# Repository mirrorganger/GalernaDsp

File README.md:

# Galerna DSP

Galerna DSP is a KiCad hardware project for an STM32-based audio effects board: two
audio channels in/out, 8 potentiometers, footswitches/buttons, an OLED display, and a
microSD slot, all built around an STM32F405.

Full design write-up — requirements, as-built BOM, power budget, codec/amp circuit
notes — lives in **[docs/Design.md](docs/Design.md)**.

## Repository layout

| Path | Contents |
|---|---|
| `GalernaDsp.kicad_pro` / `.kicad_pcb` / `.kicad_sch` | Top-level KiCad project and root schematic sheet |
| `power.kicad_sch`, `mcu.kicad_sch`, `audio_codec.kicad_sch`, `input_control.kicad_sch` | The four schematic sub-sheets |
| `libraries/Galerna/` | Project-specific KiCad symbol/footprint/3D-model library |
| `cubeMx/` | STM32CubeMX-generated firmware project for the STM32F405RGT6 (peripheral init only, no application code yet) |
| `jlcpcb/` | Manufacturing outputs for JLCPCB: gerbers, drill files, BOM/CPL for assembly |
| `docs/` | Design documentation |
| `GalernaDsp.xlsx` / `.csv` | Bill of materials |

## Opening the project

Open `GalernaDsp.kicad_pro` in KiCad (7.x). The root schematic pulls in the four
sub-sheets listed above; the PCB is a single `GalernaDsp.kicad_pcb`.

## Firmware

`cubeMx/` is a standard STM32CubeMX + CMake project. Regenerate from `cubeMx/Galerna.ioc`
in STM32CubeMX if peripheral config changes; build with CMake/CMakePresets as usual for
an STM32F4 target.

## Manufacturing

Gerbers, drill files, and JLCPCB assembly data (BOM/CPL) are pre-generated under
`jlcpcb/production_files/`.

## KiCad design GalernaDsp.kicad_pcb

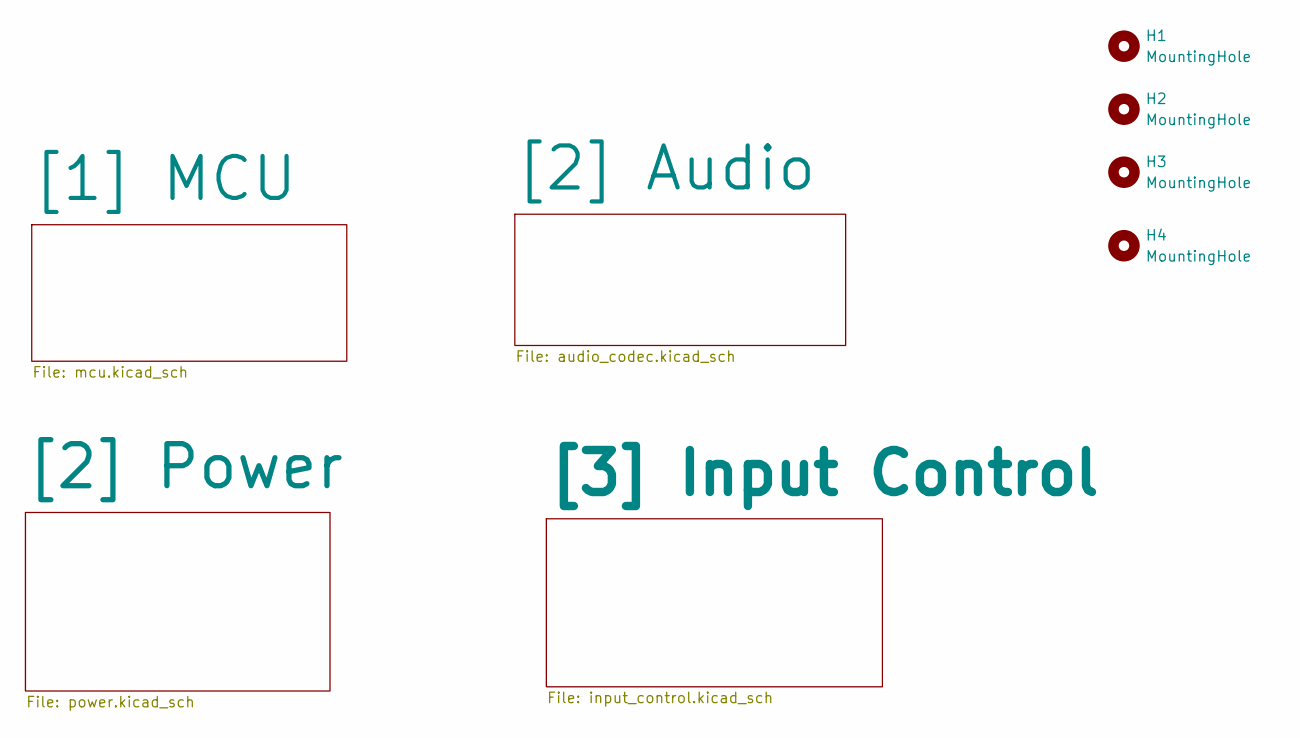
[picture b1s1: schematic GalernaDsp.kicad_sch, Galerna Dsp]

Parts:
H1, H2, H3, H4: MountingHole; MountingHole_3.2mm_M3_DIN965_Pad_TopBottom

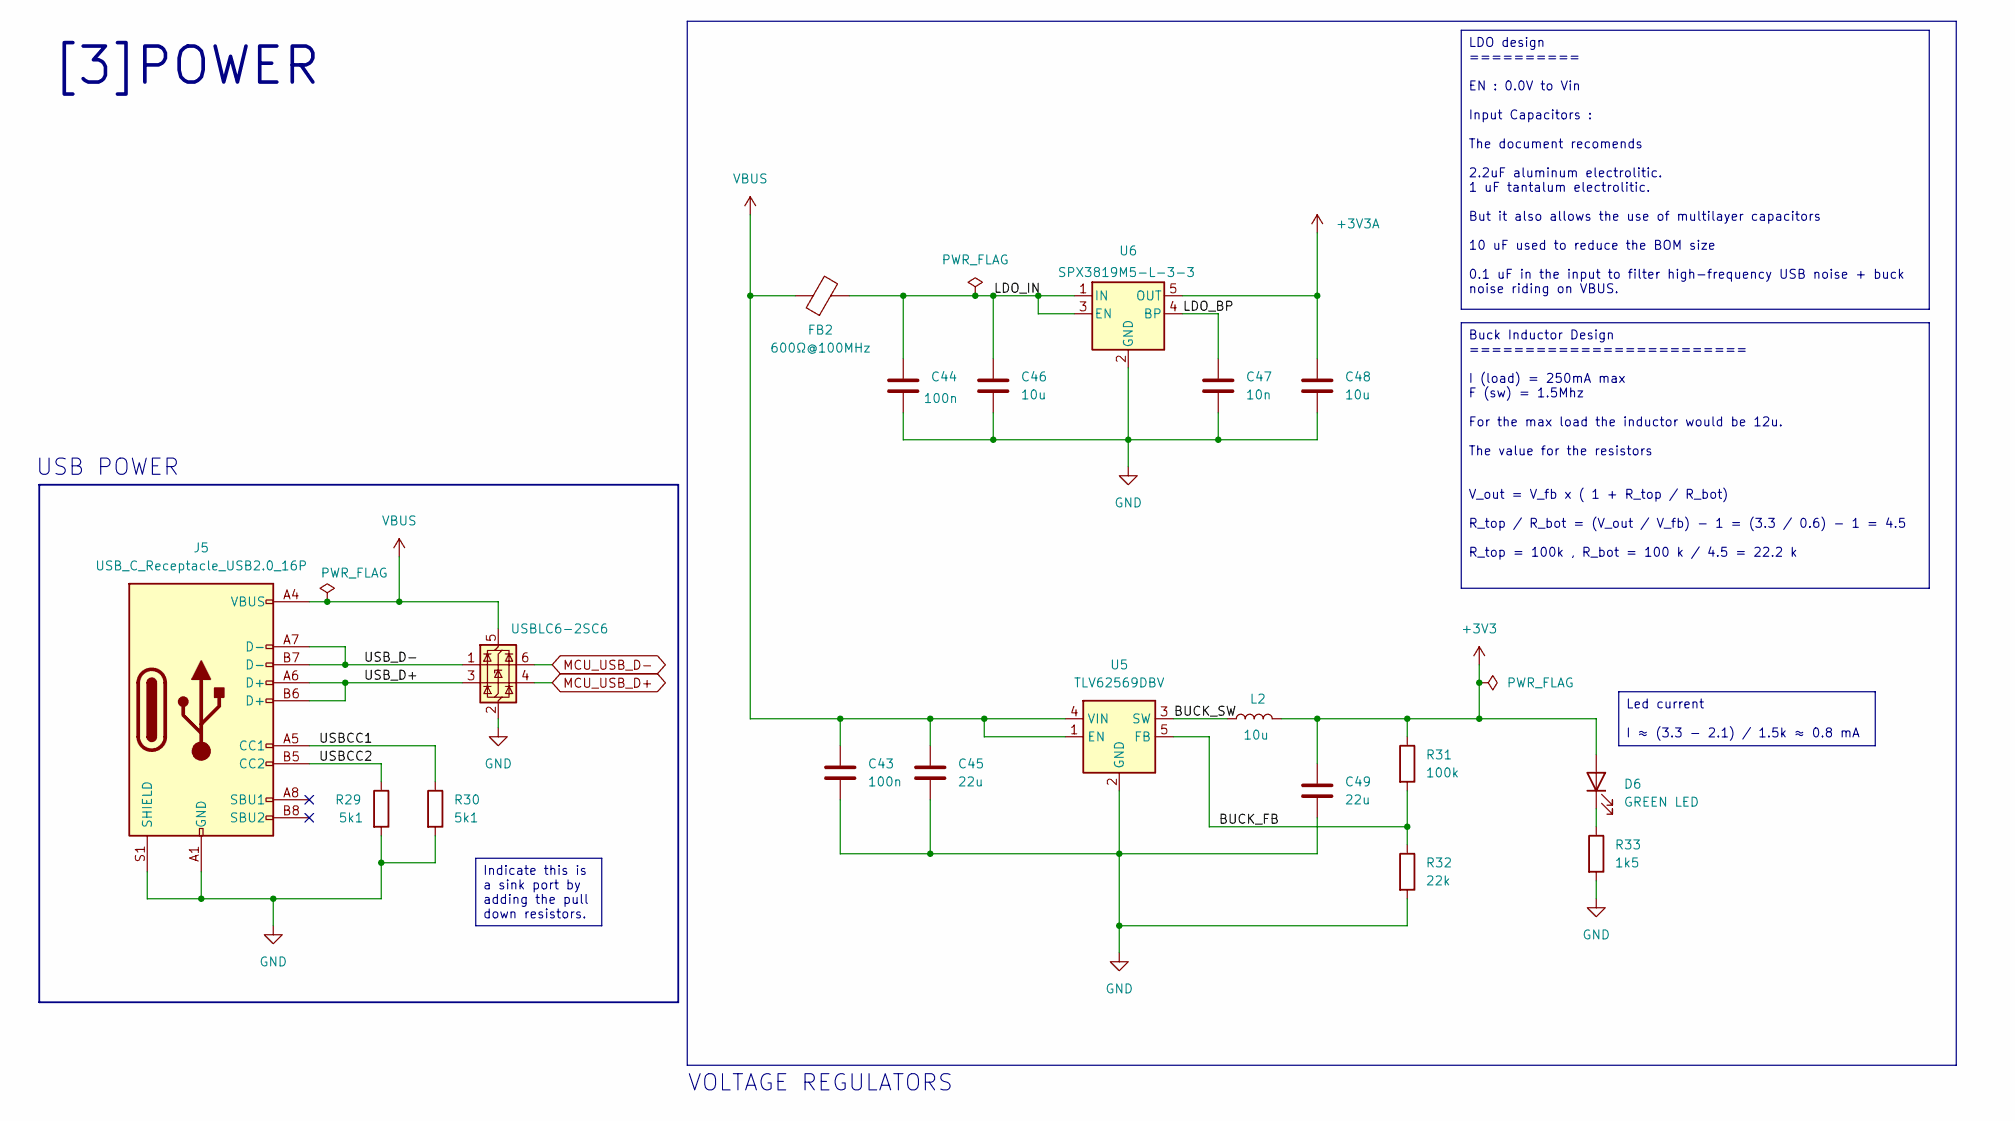
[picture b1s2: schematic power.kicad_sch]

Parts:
C43, C44: 100n; C_0402_1005Metric
C45, C49: 22u; C_0805_2012Metric
C46, C48: 10u; C_0603_1608Metric
C47: 10n; C_0402_1005Metric
D6: GREEN LED; LED_0805_2012Metric
FB2: 600Ω@100MHz; R_0805_2012Metric; Manufacturer Part GZ2012D601TF; LCSC Part C1017
J5: USB_C_Receptacle_USB2.0_16P; USB_C_Receptacle_GCT_USB4105-xx-A_16P_TopMnt_Horizontal; Manufacturer Part TYPE-C 16PIN 2MD(073); LCSC Part C2765186
L2: 10u; L_Sunlord_MWSA0618S; Manufacturer Part MWSA0618S-100MT; LCSC Part C132135
R29, R30: 5k1; R_0402_1005Metric
R31: 100k; R_0402_1005Metric
R32: 22k; R_0402_1005Metric
R33: 1k5; R_0402_1005Metric
U4: USBLC6-2SC6; SOT-23-6; Manufacturer Part USBLC6-2SC6; LCSC Part C7519
U5: TLV62569DBV; SOT-23-5; Manufacturer Part TLV62569DBVR; LCSC Part C141836
U6: SPX3819M5-L-3-3; SOT-23-5; Manufacturer Part SPX3819M5-L-3-3; LCSC Part C20617301

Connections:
+3V3: C49.1, D6.2 (A), L2.2, R31.1; also elsewhere on the board
+3V3A: C48.1, U6.5 (OUT); also elsewhere on the board
/[2] Power/BUCK_FB: R31.2, R32.1, U5.5 (FB)
/[2] Power/BUCK_SW: L2.1, U5.3 (SW)
/[2] Power/LDO_BP: C47.1, U6.4 (BP)
/[2] Power/LDO_IN: C44.1, C46.1, FB2.2, U6.1 (IN), U6.3 (EN)
/[2] Power/USBCC1: J5.A5 (CC1), R30.1
/[2] Power/USBCC2: J5.B5 (CC2), R29.1
/[2] Power/USB_D+: J5.A6 (D+), J5.B6 (D+), U4.3 (I/O2)
/[2] Power/USB_D-: J5.A7 (D-), J5.B7 (D-), U4.1 (I/O1)
GND: C43.2, C44.2, C45.2, C46.2, C47.2, C48.2, C49.2, J5.A1 (GND), J5.A12 (GND), J5.B1 (GND), J5.B12 (GND), J5.S1 (SHIELD), R29.2, R30.2, R32.2, R33.2, U4.2 (GND), U5.2 (GND), U6.2 (GND); also elsewhere on the board
MCU_USB_D+: U4.4 (I/O2); also elsewhere on the board
MCU_USB_D-: U4.6 (I/O1); also elsewhere on the board
unnamed: D6.1 (K), R33.1
VBUS: C43.1, C45.1, FB2.1, J5.A4 (VBUS), J5.A9 (VBUS), J5.B4 (VBUS), J5.B9 (VBUS), U4.5 (VBUS), U5.1 (EN), U5.4 (VIN)

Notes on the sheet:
VOLTAGE REGULATORS
USB POWER
[3]POWER
Indicate this is a sink port by adding the pull down resistors.
Led current I ≈ (3.3 - 2.1) / 1.5k ≈ 0.8 mA
LDO design ========== EN : 0.0V to Vin Input Capacitors : The document recomends 2.2uF aluminum electrolitic. 1 uF tantalum electrolitic. But it also allows the use of multilayer capacitors 10 uF used to reduce the BOM size 0.1 uF in the input to filter high-frequency USB noise + buck noise riding 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
Buck Inductor Design ========================= I (load) = 250mA max F (sw) = 1.5Mhz For the max load the inductor would be 12u. The value for the resistors V_out = V_fb x ( 1 + R_top / R_bot) R_top / R_bot = (V_out / V_fb) - 1 = (3.3 / 0.6) - 1 = 4.5 R_top = 100k , R_bot = 100 k / 4.5 = 22.2 k

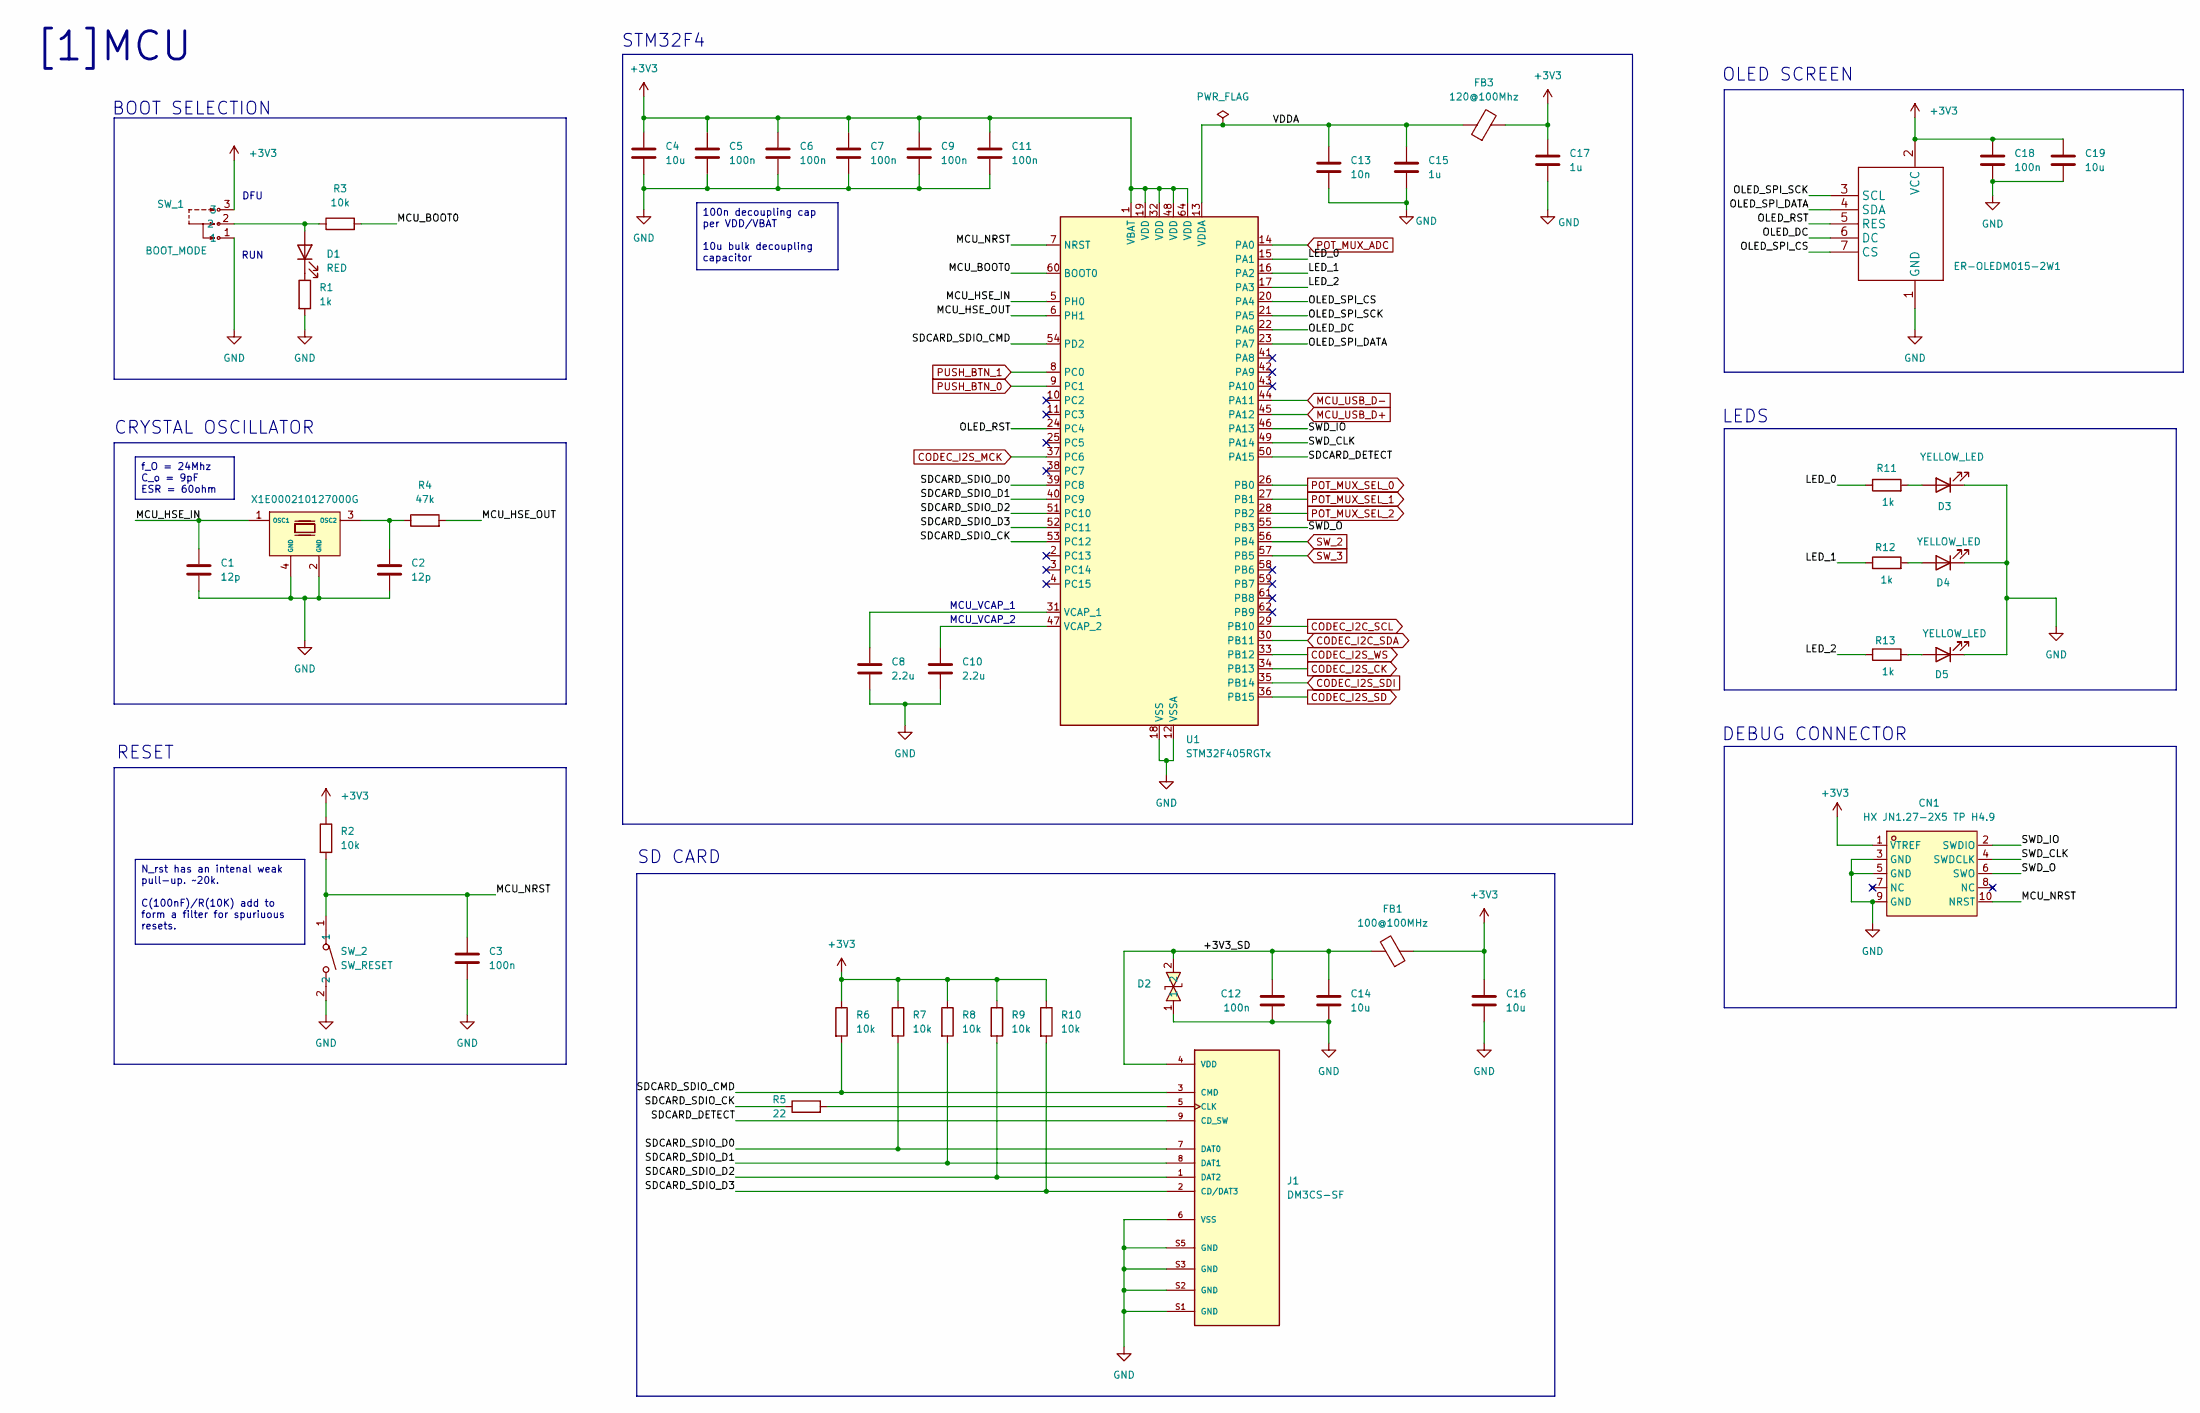
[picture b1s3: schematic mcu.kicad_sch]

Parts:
C1, C2: 12p; C_0402_1005Metric
C3, C5, C6, C7, C9, C11, C12, C18: 100n; C_0402_1005Metric
C4, C14, C16, C19: 10u; C_0603_1608Metric
C8, C10: 2.2u; C_0805_2012Metric
C13: 10n; C_0402_1005Metric
C15, C17: 1u; C_0603_1608Metric
CN1: HX JN1.27-2X5 TP H4.9; IDC-SMD_10P-P1.27-3220-10-0300-00; Manufacturer Part HX JN1.27-2x5 TP H4.9; LCSC Part C42372555
D1: RED; LED_0603_1608Metric
D2: RCLAMP0521P-N; X1-DFN1006-2_L1.0-W0.6-P0.65-BI; Manufacturer Part RCLAMP0521P-N; LCSC Part C316043
D3, D4, D5: YELLOW_LED; LED_0603_1608Metric
ER-OLEDM015-2W1: ER-OLEDM015-2
FB1: 100@100MHz; L_0805_2012Metric
FB3: 120@100Mhz; R_0603_1608Metric
J1: DM3CS-SF; HRS_DM3CS-SF; PARTREV n/a; LCSC Part C202111
R1: 1k; R_0402_1005Metric; Manufacturer Part 0402WGF1001TCE; LCSC Part C11702
R2, R3, R6, R7, R8, R9, R10: 10k; R_0402_1005Metric
R4: 47k; R_0402_1005Metric
R5: 22; R_0402_1005Metric
R11, R12, R13: 1k; R_0402_1005Metric
SW_1: BOOT_MODE; SW-TH_SHOU-HAN_SS12D10G4; Manufacturer Part SS12D10G5; LCSC Part C7431054
SW_2: SW_RESET; SW-SMD_L3.9-W3.0-P4.45; Manufacturer Part TS-1088-AR02016; LCSC Part C720477
U1: STM32F405RGTx; LQFP-64_10x10mm_P0.5mm; Manufacturer Part STM32F405RGT6; LCSC Part C15742
X1: X1E000210127000G; CRYSTAL-SMD_4P-L3.2-W2.5-BL; Manufacturer Part X1E0000210127; LCSC Part C89577

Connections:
+3V3: C4.1, C5.1, C6.1, C7.1, C9.1, C11.1, C16.1, C17.1, C18.1, C19.1, CN1.1 (VTREF), ER-OLEDM015-2W1.2 (VCC), FB1.1, FB3.2, R2.1, R6.1, R7.1, R8.1, R9.1, R10.1, SW_1.3, U1.1 (VBAT), U1.19 (VDD), U1.32 (VDD), U1.48 (VDD), U1.64 (VDD); also elsewhere on the board
/[1] MCU/+3V3_SD: C12.1, C14.1, D2.2, FB1.2, J1.4 (VDD)
/[1] MCU/LED_0: R11.1, U1.15 (PA1)
/[1] MCU/LED_1: R12.1, U1.16 (PA2)
/[1] MCU/LED_2: R13.1, U1.17 (PA3)
/[1] MCU/MCU_BOOT0: R3.2, U1.60 (BOOT0)
/[1] MCU/MCU_HSE_IN: C1.1, U1.5 (PH0), X1.1 (OSC1)
/[1] MCU/MCU_HSE_OUT: R4.2, U1.6 (PH1)
/[1] MCU/MCU_NRST: C3.1, CN1.10 (NRST), R2.2, SW_2.1, U1.7 (NRST)
/[1] MCU/OLED_DC: ER-OLEDM015-2W1.6 (DC), U1.22 (PA6)
/[1] MCU/OLED_RST: ER-OLEDM015-2W1.5 (RES), U1.24 (PC4)
/[1] MCU/OLED_SPI_CS: ER-OLEDM015-2W1.7 (CS), U1.20 (PA4)
/[1] MCU/OLED_SPI_DATA: ER-OLEDM015-2W1.4 (SDA), U1.23 (PA7)
/[1] MCU/OLED_SPI_SCK: ER-OLEDM015-2W1.3 (SCL), U1.21 (PA5)
/[1] MCU/SDCARD_DETECT: J1.9 (CD_SW), U1.50 (PA15)
/[1] MCU/SDCARD_SDIO_CK: R5.1, U1.53 (PC12)
/[1] MCU/SDCARD_SDIO_CMD: J1.3 (CMD), R6.2, U1.54 (PD2)
/[1] MCU/SDCARD_SDIO_D0: J1.7 (DAT0), R7.2, U1.39 (PC8)
/[1] MCU/SDCARD_SDIO_D1: J1.8 (DAT1), R8.2, U1.40 (PC9)
/[1] MCU/SDCARD_SDIO_D2: J1.1 (DAT2), R9.2, U1.51 (PC10)
/[1] MCU/SDCARD_SDIO_D3: J1.2 (CD/DAT3), R10.2, U1.52 (PC11)
/[1] MCU/SWD_CLK: CN1.4 (SWDCLK), U1.49 (PA14)
/[1] MCU/SWD_IO: CN1.2 (SWDIO), U1.46 (PA13)
/[1] MCU/SWD_O: CN1.6 (SWO), U1.55 (PB3)
/[1] MCU/VDDA: C13.1, C15.1, FB3.1, U1.13 (VDDA)
CODEC_I2C_SCL: U1.29 (PB10); also elsewhere on the board
CODEC_I2C_SDA: U1.30 (PB11); also elsewhere on the board
CODEC_I2S_CK: U1.34 (PB13); also elsewhere on the board
CODEC_I2S_MCK: U1.37 (PC6); also elsewhere on the board
CODEC_I2S_SD: U1.36 (PB15); also elsewhere on the board
CODEC_I2S_SDI: U1.35 (PB14); also elsewhere on the board
CODEC_I2S_WS: U1.33 (PB12); also elsewhere on the board
GND: C1.2, C2.2, C3.2, C4.2, C5.2, C6.2, C7.2, C8.2, C9.2, C10.2, C11.2, C12.2, C13.2, C14.2, C15.2, C16.2, C17.2, C18.2, C19.2, CN1.3 (GND), CN1.5 (GND), CN1.9 (GND), D2.1, D3.1 (K), D4.1 (K), D5.1 (K), ER-OLEDM015-2W1.1 (GND), J1.6 (VSS), J1.S1 (GND), J1.S2 (GND), J1.S3 (GND), J1.S5 (GND), R1.2, SW_1.1, SW_2.2, U1.12 (VSSA), U1.18 (VSS), U1.63 (VSS), X1.2 (GND), X1.4 (GND); also elsewhere on the board
MCU_USB_D+: U1.45 (PA12); also elsewhere on the board
MCU_USB_D-: U1.44 (PA11); also elsewhere on the board
unnamed: D1.2 (A), R3.1, SW_1.2
unnamed: D1.1 (K), R1.1
unnamed: D3.2 (A), R11.2
unnamed: D4.2 (A), R12.2
unnamed: D5.2 (A), R13.2
unnamed: J1.5 (CLK), R5.2
unnamed: C8.1, U1.31 (VCAP_1)
unnamed: C10.1, U1.47 (VCAP_2)
unnamed: C2.1, R4.1, X1.3 (OSC2)
POT_MUX_ADC: U1.14 (PA0); also elsewhere on the board
POT_MUX_SEL_0: U1.26 (PB0); also elsewhere on the board
POT_MUX_SEL_1: U1.27 (PB1); also elsewhere on the board
POT_MUX_SEL_2: U1.28 (PB2); also elsewhere on the board
PUSH_BTN_0: U1.9 (PC1); also elsewhere on the board
PUSH_BTN_1: U1.8 (PC0); also elsewhere on the board
SW_2: U1.56 (PB4); also elsewhere on the board
SW_3: U1.57 (PB5); also elsewhere on the board

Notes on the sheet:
[1]MCU
RUN
BOOT SELECTION
SD CARD
LEDS
MCU_VCAP_2
DEBUG CONNECTOR
RESET
OLED SCREEN
STM32F4
MCU_VCAP_1
CRYSTAL OSCILLATOR
DFU
100n decoupling cap per VDD/VBAT 10u bulk decoupling capacitor
f_O = 24Mhz C_o = 9pF ESR = 60ohm
N_rst has an intenal weak pull-up. ~20k. C(100nF)/R(10K) add to form a filter for spuriuous resets.

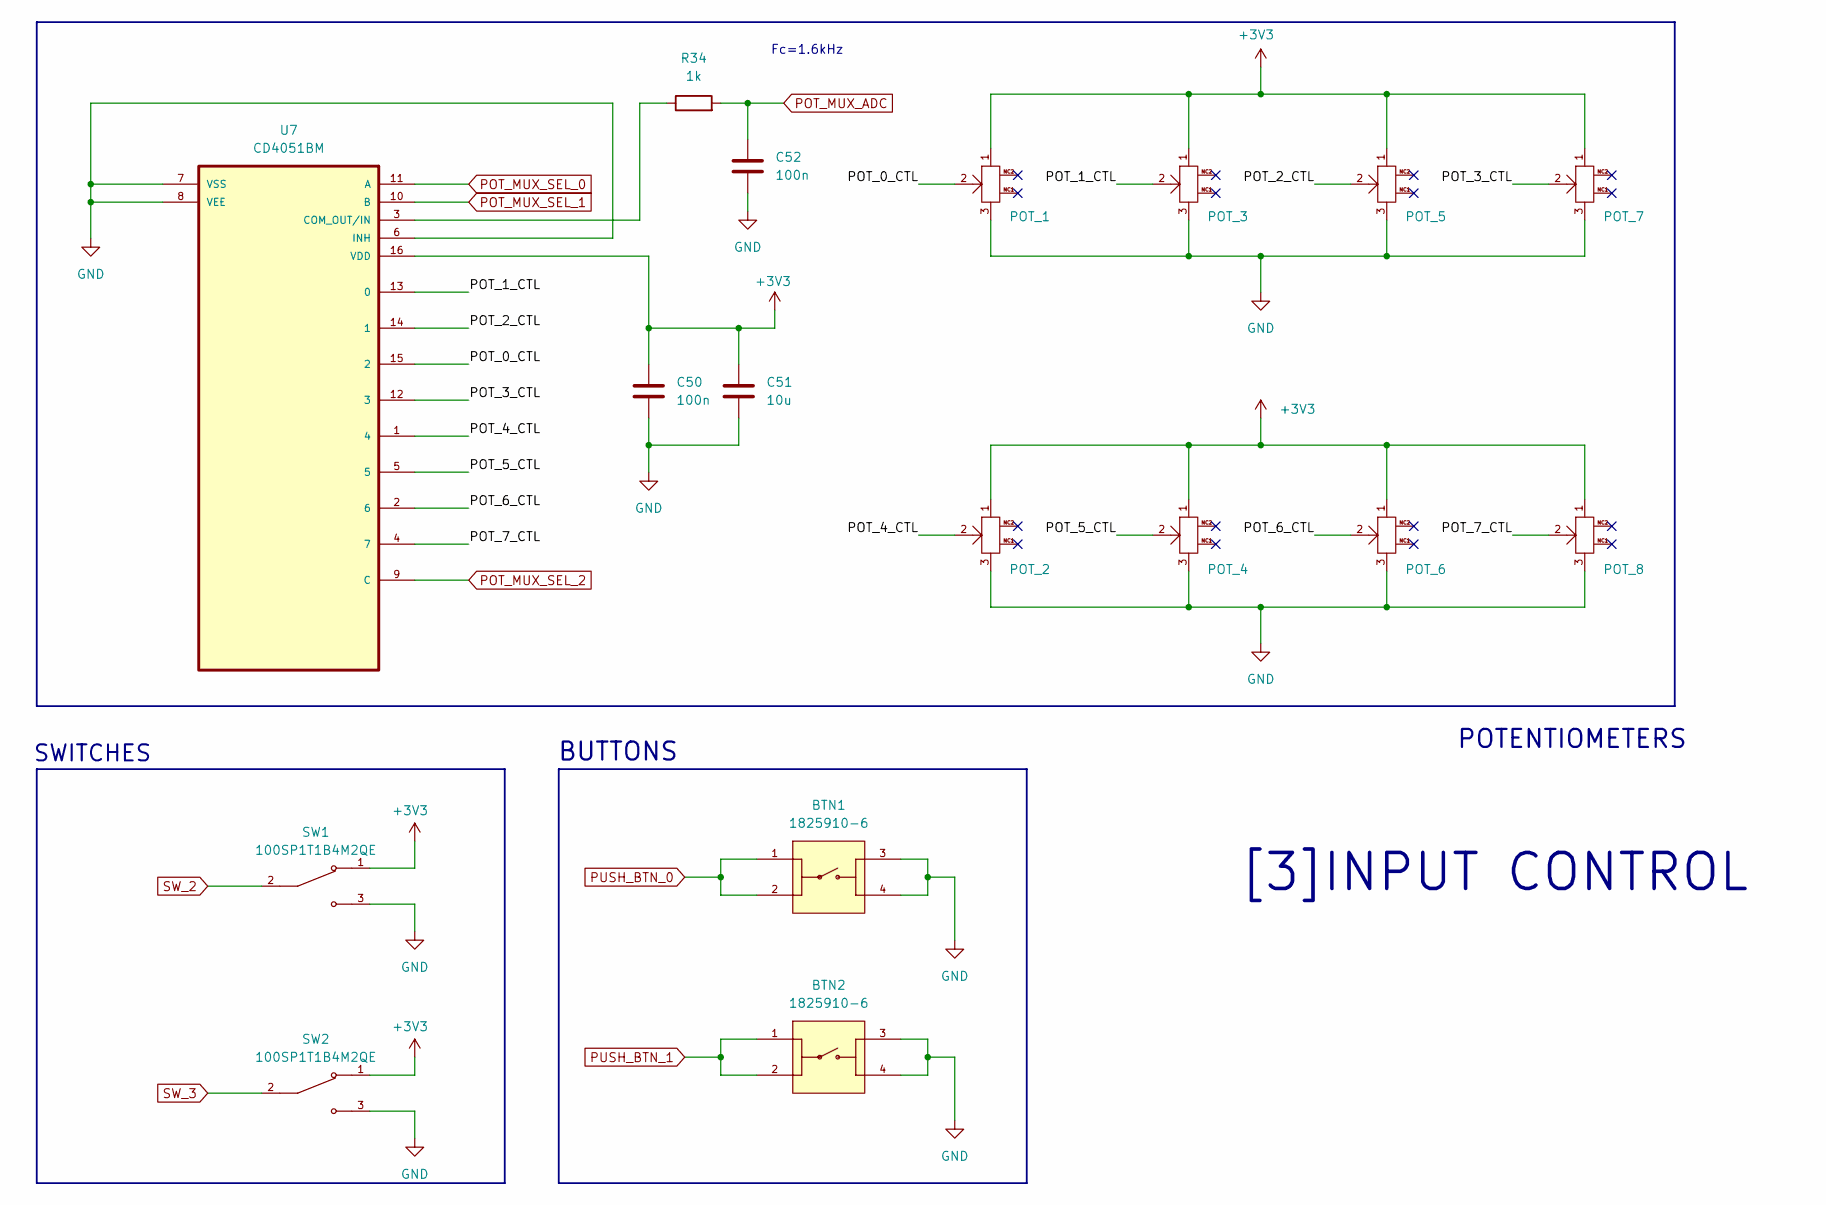
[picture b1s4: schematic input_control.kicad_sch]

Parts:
BTN1, BTN2: 1825910-6; SW4_1825910-B_TEC; PARTREV C10
C50, C52: 100n; C_0402_1005Metric
C51: 10u; C_0603_1608Metric
POT_1, POT_2, POT_3, POT_4, POT_5, POT_6, POT_7, POT_8: PTV09A-4225F-B104; PTV09; PARTNO PTV09A-4225F-B104-ND; LCSC Part C5848796
R34: 1k; R_0402_1005Metric; Manufacturer Part 0402WGF1001TCE; LCSC Part C11702
SW1, SW2: 100SP1T1B4M2QE; SW_100SP1T1B4M2QE; PARTREV E; LCSC Part C273353
U7: CD4051BM; SOIC127P600X175-16N; Manufacturer Part CD4051BM96; LCSC Part C21379

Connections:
+3V3: C50.1, C51.1, POT_1.1, POT_2.1, POT_3.1, POT_4.1, POT_5.1, POT_6.1, POT_7.1, POT_8.1, SW1.1, SW2.1, U7.16 (VDD); also elsewhere on the board
/[3] Input Control/POT_0_CTL: POT_1.2, U7.15 (2)
/[3] Input Control/POT_1_CTL: POT_3.2, U7.13 (0)
/[3] Input Control/POT_2_CTL: POT_5.2, U7.14 (1)
/[3] Input Control/POT_3_CTL: POT_7.2, U7.12 (3)
/[3] Input Control/POT_4_CTL: POT_2.2, U7.1 (4)
/[3] Input Control/POT_5_CTL: POT_4.2, U7.5
/[3] Input Control/POT_6_CTL: POT_6.2, U7.2 (6)
/[3] Input Control/POT_7_CTL: POT_8.2, U7.4 (7)
GND: BTN1.3, BTN1.4, BTN2.3, BTN2.4, C50.2, C51.2, C52.2, POT_1.3, POT_2.3, POT_3.3, POT_4.3, POT_5.3, POT_6.3, POT_7.3, POT_8.3, SW1.3, SW2.3, U7.6 (INH), U7.7 (VSS), U7.8 (VEE); also elsewhere on the board
unnamed: R34.1, U7.3 (COM_OUT/IN)
POT_MUX_ADC: C52.1, R34.2; also elsewhere on the board
POT_MUX_SEL_0: U7.11 (A); also elsewhere on the board
POT_MUX_SEL_1: U7.10 (B); also elsewhere on the board
POT_MUX_SEL_2: U7.9 (C); also elsewhere on the board
PUSH_BTN_0: BTN1.1, BTN1.2; also elsewhere on the board
PUSH_BTN_1: BTN2.1, BTN2.2; also elsewhere on the board
SW_2: SW1.2; also elsewhere on the board
SW_3: SW2.2; also elsewhere on the board

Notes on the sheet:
BUTTONS
SWITCHES
POTENTIOMETERS
[3]INPUT CONTROL
Fc=1.6kHz

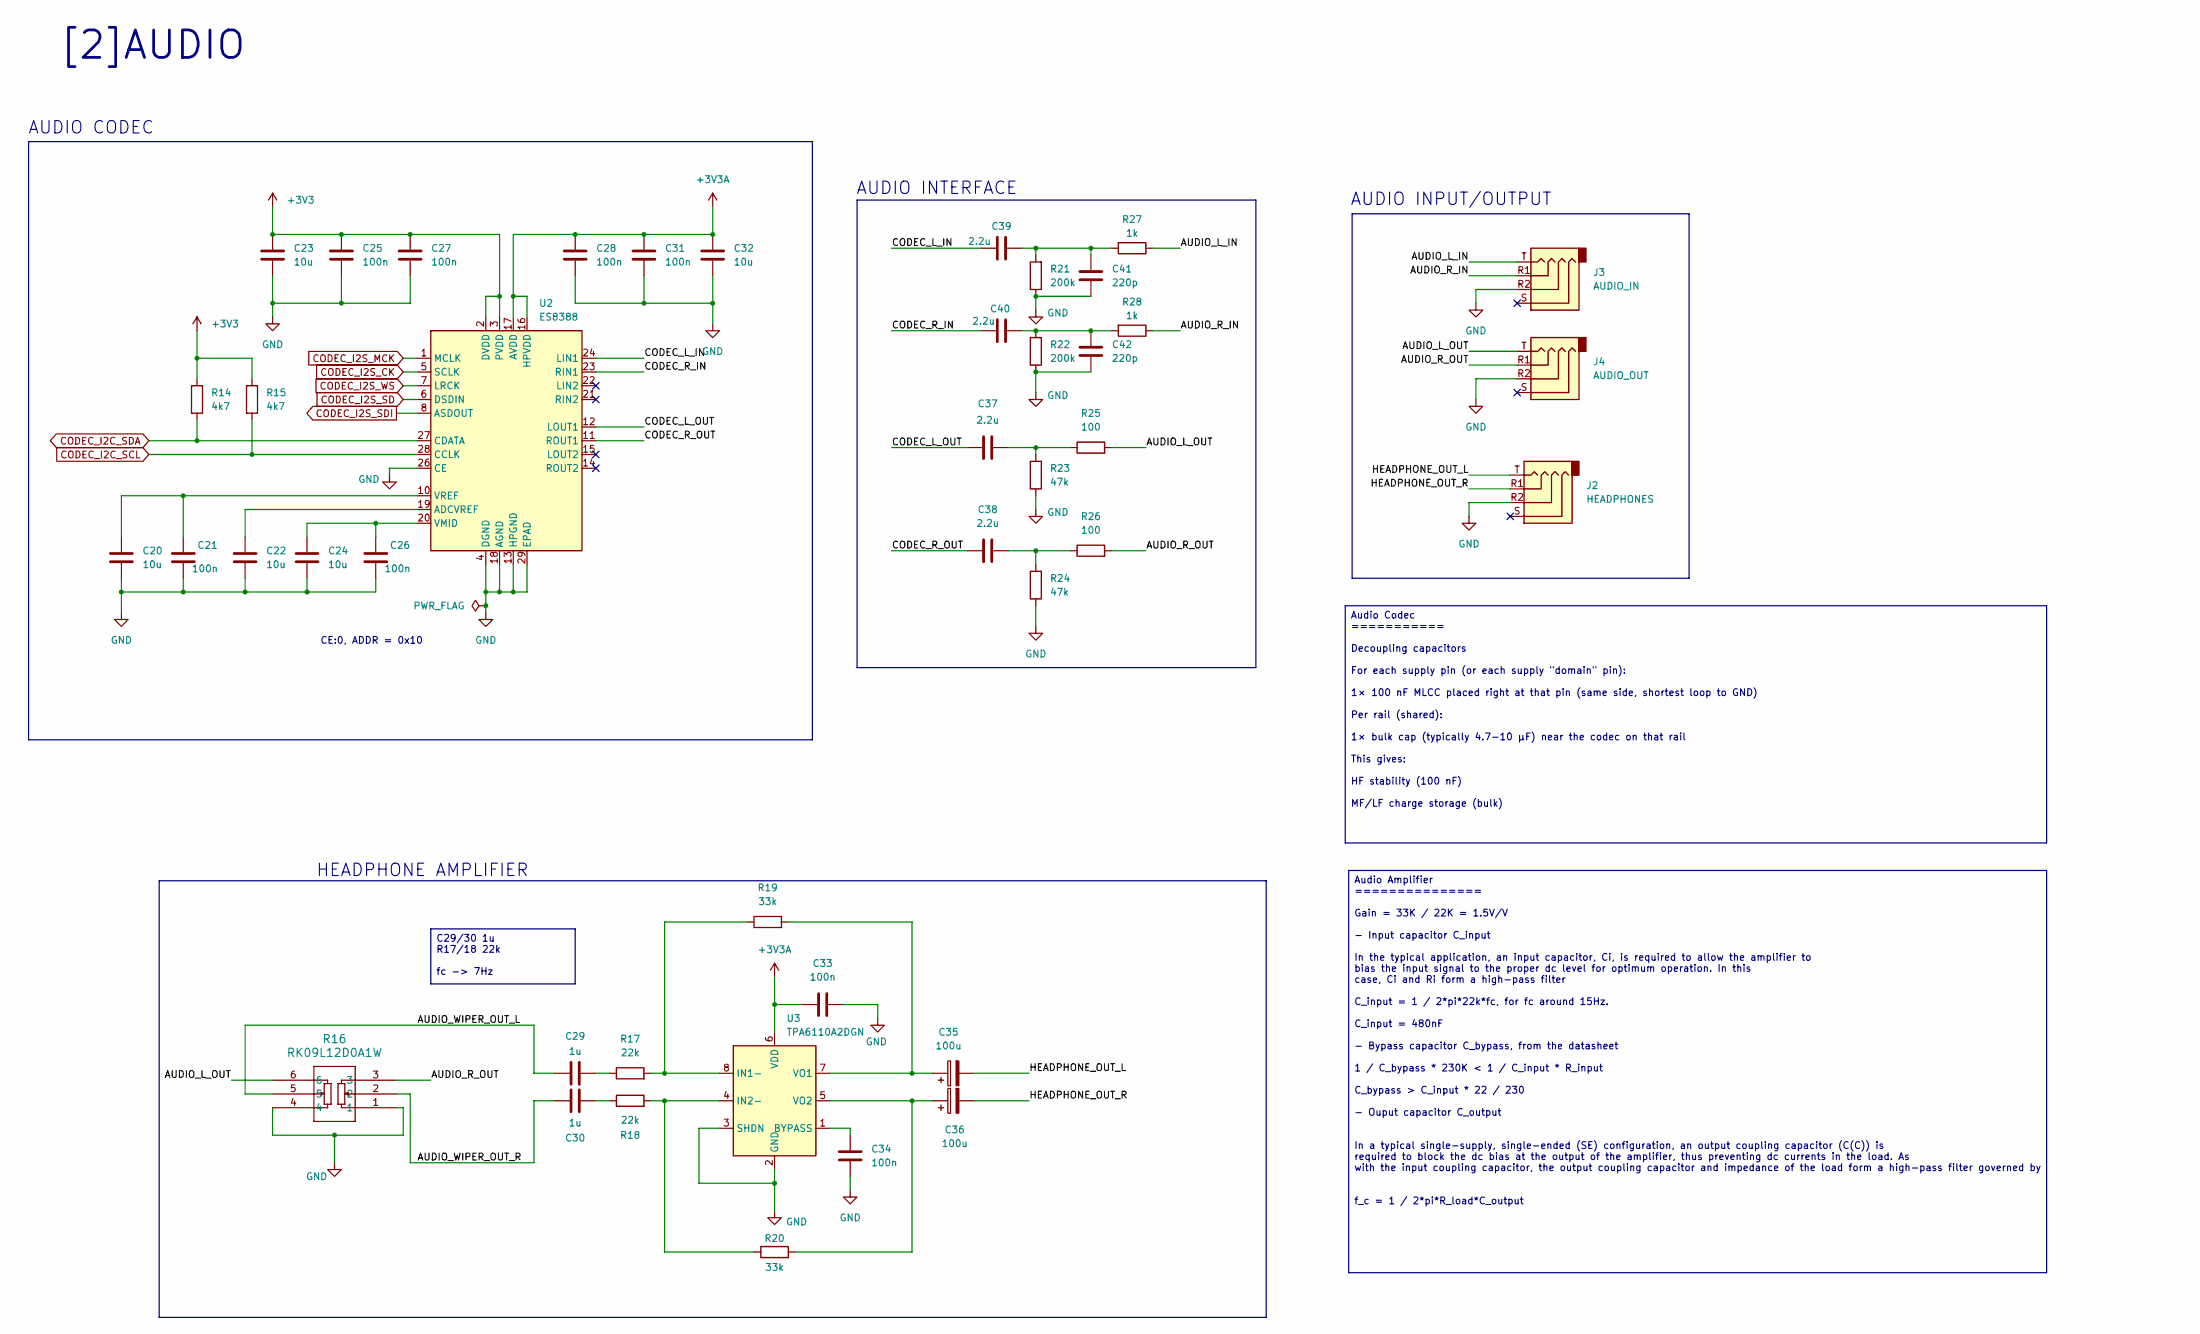
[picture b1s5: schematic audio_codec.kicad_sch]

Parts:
C20, C22, C23, C24, C32: 10u; C_0603_1608Metric
C21, C25, C26, C27, C28, C31, C33, C34: 100n; C_0402_1005Metric
C29, C30: 1u; C_0402_1005Metric
C35, C36: 100u; CHEMI-F80
C37, C38, C39, C40: 2.2u; C_0805_2012Metric
C41, C42: 220p; C_0402_1005Metric
J2: HEADPHONES; AUDIO-SMD_PJ-320D-1
J3: AUDIO_IN; AUDIO-SMD_PJ-320D-1
J4: AUDIO_OUT; AUDIO-SMD_PJ-320D-1
R14, R15: 4k7; R_0402_1005Metric
R16: RK09L12D0A1W; RK09L12D0A1W_AAL; Manufacturer Part RK09L12D0A1W; LCSC Part C470487
R17, R18: 22k; R_0402_1005Metric
R19, R20: 33k; R_0402_1005Metric
R21, R22: 200k; R_0402_1005Metric
R23, R24: 47k; R_0402_1005Metric
R25, R26: 100; R_0402_1005Metric
R27, R28: 1k; R_0402_1005Metric; Manufacturer Part 0402WGF1001TCE; LCSC Part C11702
U2: ES8388; Manufacturer Part ES8388; LCSC Part C365736
U3: TPA6110A2DGN; HVSSOP-8-1EP_3x3mm_P0.65mm_EP1.57x1.89mm; Manufacturer Part TPA6110A2DGNR; LCSC Part C130212

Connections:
+3V3: C23.1, C25.1, C27.1, R14.1, R15.1, U2.2 (DVDD), U2.3 (PVDD); also elsewhere on the board
+3V3A: C28.1, C31.1, C32.1, C33.2, U2.16 (HPVDD), U2.17 (AVDD), U3.6 (VDD); also elsewhere on the board
/[2] Audio/AUDIO_L_IN: J3.T, R27.1
/[2] Audio/AUDIO_L_OUT: J4.T, R16.6, R25.2
/[2] Audio/AUDIO_R_IN: J3.R1, R28.1
/[2] Audio/AUDIO_R_OUT: J4.R1, R16.3, R26.2
/[2] Audio/AUDIO_WIPER_OUT_L: C29.1, R16.5
/[2] Audio/AUDIO_WIPER_OUT_R: C30.1, R16.2
/[2] Audio/CODEC_L_IN: C39.2, U2.24 (LIN1)
/[2] Audio/CODEC_L_OUT: C37.2, U2.12 (LOUT1)
/[2] Audio/CODEC_R_IN: C40.2, U2.23 (RIN1)
/[2] Audio/CODEC_R_OUT: C38.2, U2.11 (ROUT1)
/[2] Audio/HEADPHONE_OUT_L: C35.2, J2.T
/[2] Audio/HEADPHONE_OUT_R: C36.2, J2.R1
CODEC_I2C_SCL: R15.2, U2.28 (CCLK); also elsewhere on the board
CODEC_I2C_SDA: R14.2, U2.27 (CDATA); also elsewhere on the board
CODEC_I2S_CK: U2.5 (SCLK); also elsewhere on the board
CODEC_I2S_MCK: U2.1 (MCLK); also elsewhere on the board
CODEC_I2S_SD: U2.6 (DSDIN); also elsewhere on the board
CODEC_I2S_SDI: U2.8 (ASDOUT); also elsewhere on the board
CODEC_I2S_WS: U2.7 (LRCK); also elsewhere on the board
GND: C20.2, C21.2, C22.2, C23.2, C24.2, C25.2, C26.2, C27.2, C28.2, C31.2, C32.2, C33.1, C34.1, C41.2, C42.2, J2.R2, J3.R2, J4.R2, R16.1, R16.4, R21.1, R22.1, R23.1, R24.1, U2.4 (DGND), U2.13 (HPGND), U2.18 (AGND), U2.26 (CE), U2.29 (EPAD), U3.2 (GND), U3.3 (SHDN), U3.9 (GND); also elsewhere on the board
unnamed: C29.2, R17.1
unnamed: C30.2, R18.1
unnamed: C37.1, R23.2, R25.1
unnamed: C38.1, R24.2, R26.1
unnamed: C39.1, C41.1, R21.2, R27.2
unnamed: C40.1, C42.1, R22.2, R28.2
unnamed: C22.1, U2.19 (ADCVREF)
unnamed: C24.1, C26.1, U2.20 (VMID)
unnamed: C20.1, C21.1, U2.10 (VREF)
unnamed: C34.2, U3.1 (BYPASS)
unnamed: R17.2, R19.1, U3.8 (IN1-)
unnamed: R18.2, R20.1, U3.4 (IN2-)
unnamed: C35.1, R19.2, U3.7 (VO1)
unnamed: C36.1, R20.2, U3.5 (VO2)

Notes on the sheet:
AUDIO CODEC
AUDIO INPUT/OUTPUT
CE:0, ADDR = 0x10
HEADPHONE AMPLIFIER
AUDIO INTERFACE
[2]AUDIO
C29/30 1u R17/18 22k fc -> 7Hz
Audio Codec =========== Decoupling capacitors For each supply pin (or each supply "domain" pin): 1× 100 nF MLCC placed right at that pin (same side, shortest loop to GND) Per rail (shared): 1× bulk cap (typically 4.7-10 µF) near the codec on that rail This gives: HF stability (100 nF) MF/LF charge 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
Audio Amplifier =============== Gain = 33K / 22K = 1.5V/V - Input capacitor C_input In the typical application, an input capacitor, Ci, is required to allow the amplifier to bias the input signal to the proper dc level for optimum operation. In this case, Ci and Ri form a high-pass filter C_input =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

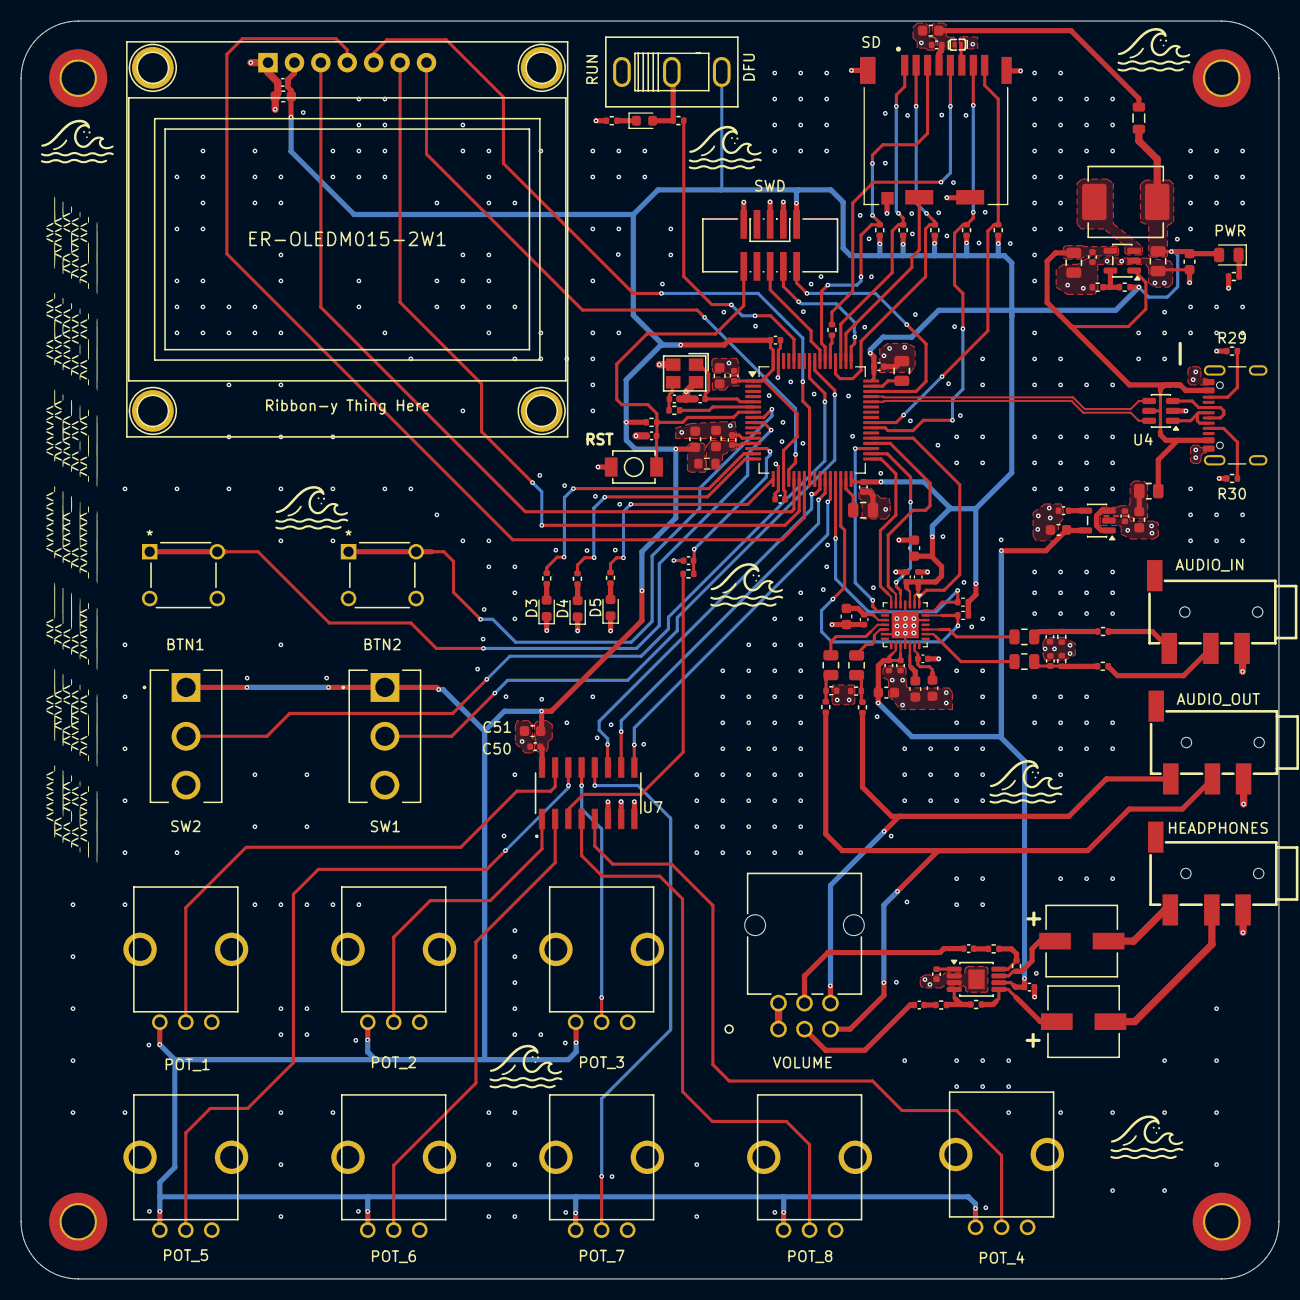
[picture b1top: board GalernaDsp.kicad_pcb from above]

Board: 4 copper layers, 121.0 x 121.0 mm, 129 parts (0 on the bottom side), 98 nets.

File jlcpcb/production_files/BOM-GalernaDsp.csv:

Comment,Designator,Footprint,LCSC,Quantity
100,"R25,R26",R_0402_1005Metric,C25076,2
100@100MHz,FB1,L_0805_2012Metric,C1015,1
100SP1T1B4M2QE,"SW1,SW2",SW_100SP1T1B4M2QE,C273353,2
100k,R31,R_0402_1005Metric,C25741,1
100n,"C11,C12,C18,C21,C25,C26,C27,C28,C3,C31,C33,C34,C43,C44,C5,C50,C52,C6,C7,C9",C_0402_1005Metric,C1525,20
100u,"C35,C36",CHEMI-F80,C2162906,2
10k,"R10,R2,R3,R6,R7,R8,R9",R_0402_1005Metric,C25744,7
10n,"C13,C47",C_0402_1005Metric,C15195,2
10u,L2,L_Sunlord_MWSA0618S,C132135,1
10u,"C14,C16,C19,C20,C22,C23,C24,C32,C4,C46,C48,C51",C_0603_1608Metric,C19702,12
120@100Mhz,FB3,R_0603_1608Metric,C14709,1
12p,"C1,C2",C_0402_1005Metric,C1547,2
1825910-6,"BTN1,BTN2",SW4_1825910-B_TEC,C428628,2
1k,"R1,R11,R12,R13,R27,R28,R34",R_0402_1005Metric,C11702,7
1k5,R33,R_0402_1005Metric,C25867,1
1u,"C15,C17",C_0603_1608Metric,C15849,2
1u,"C29,C30",C_0402_1005Metric,C52923,2
2.2u,"C10,C37,C38,C39,C40,C8",C_0805_2012Metric,C377773,6
200k,"R21,R22",R_0402_1005Metric,C25764,2
22,R5,R_0402_1005Metric,C25092,1
220p,"C41,C42",C_0402_1005Metric,C1530,2
22k,"R17,R18,R32",R_0402_1005Metric,C25768,3
22u,"C45,C49",C_0805_2012Metric,C45783,2
33k,"R19,R20",R_0402_1005Metric,C25779,2
47k,"R23,R24,R4",R_0402_1005Metric,C25792,3
4k7,"R14,R15",R_0402_1005Metric,C25900,2
5k1,"R29,R30",R_0402_1005Metric,C25905,2
600Ω@100MHz,FB2,R_0805_2012Metric,C1017,1
JACK,"J2,J3,J4",AUDIO-SMD_PJ-320D-1,C431535,1
BOOT_MODE,SW_1,SW-TH_SHOU-HAN_SS12D10G4,C7431054,1
CD4051BM,U7,SOIC127P600X175-16N,C21379,1
DM3CS-SF,J1,HRS_DM3CS-SF,C202111,1
ES8388,U2,ES8388,C365736,1
GREEN LED,D6,LED_0805_2012Metric,C2297,1
HX JN1.27-2X5 TP H4.9,CN1,IDC-SMD_10P-P1.27-3220-10-0300-00,C42372555,1
PTV09A-4225F-B104,"POT_1,POT_2,POT_3,POT_4,POT_5,POT_6,POT_7,POT_8",PTV09,C5848796,8
RCLAMP0521P-N,D2,X1-DFN1006-2_L1.0-W0.6-P0.65-BI,C316043,1
RED,D1,LED_0603_1608Metric,C2286,1
RK09L12D0A1W,R16,RK09L12D0A1W_AAL,C470487,1
SPX3819M5-L-3-3,U6,SOT-23-5,C20617301,1
STM32F405RGTx,U1,LQFP-64_10x10mm_P0.5mm,C15742,1
SW_RESET,SW_2,SW-SMD_L3.9-W3.0-P4.45,C720477,1
TLV62569DBV,U5,SOT-23-5,C141836,1
TPA6110A2DGN,U3,HVSSOP-8-1EP_3x3mm_P0.65mm_EP1.57x1.89mm,C130212,1
USBLC6-2SC6,U4,SOT-23-6,C7519,1
USB_C_Receptacle_USB2.0_16P,J5,USB_C_Receptacle_GCT_USB4105-xx-A_16P_TopMnt_Horizontal,C2765186,1
X1E000210127000G,X1,CRYSTAL-SMD_4P-L3.2-W2.5-BL,C89577,1
YELLOW_LED,"D3,D4,D5",LED_0603_1608Metric,C2290,3

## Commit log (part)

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2026-01-31 adding git ignore
2026-01-31 pushing project
2026-02-01 Audio schematic updated
2026-02-01 Added oled
2026-02-03 SWD connector added
2026-02-04 extending library
2026-02-05 adde boot switch
2026-02-05 updating ignore file
2026-02-08 First pins assingments
2026-02-09 MCU connected
2026-02-09 adding anotations
2026-02-10 ERC fixed
2026-02-11 footprints updated
2026-02-11 footprint updated
2026-02-12 pcb setup
2026-02-12 decoupling caps route
2026-02-14 constraints updated
2026-02-14 rules updated
2026-02-17 codec placed
2026-02-18 edge cuts with rectangle
2026-02-18 cube mx project
2026-02-18 extending gitignore
2026-02-18 control positioned
2026-02-22 extending libraries
2026-02-22 updating names
2026-02-23 net classes added
2026-03-01 routing update
2026-03-03 last updates
2026-03-03 updated placement
2026-03-05 addic doc
2026-03-14 headphone amplifier routing
2026-03-19 pcb updated
2026-04-05 last update
2026-04-08 last status
2026-04-09 Fixing main DRC on pcb
2026-04-13 DRC fixes
2026-04-14 All DRC fixed
2026-04-26 Codec updated to ES8388 on schematic
2026-05-03 ES8388 placed
2026-05-13 saving state
2026-05-13 Adding xlsx bom
2026-05-13 fillin info in parts
2026-05-31 JLC order
